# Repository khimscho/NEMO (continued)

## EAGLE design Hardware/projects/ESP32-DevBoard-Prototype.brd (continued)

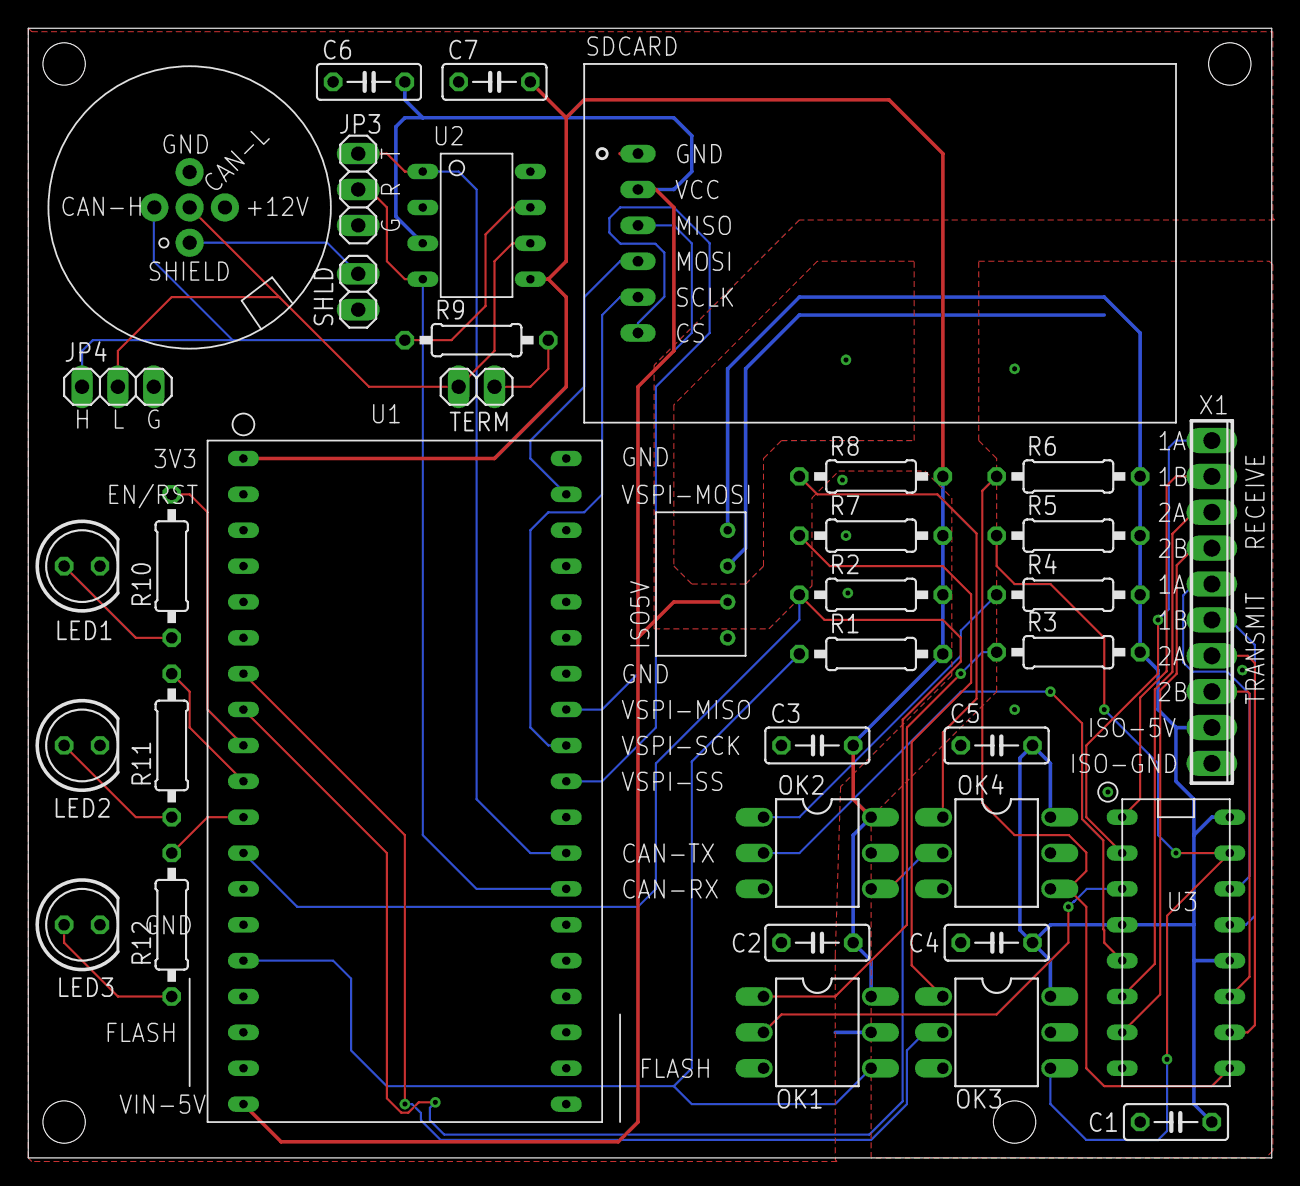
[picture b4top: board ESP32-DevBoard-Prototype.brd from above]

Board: 2 copper layers, 88.1 x 80.0 mm, 37 parts (0 on the bottom side), 41 nets.

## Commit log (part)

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2021-02-16 Fixed bug in StatusLED that was preventing blue channel from working.
2021-02-26 Cleaned up reporting of debugging information (efficiency).
2021-03-05 Added debugging facility for a dummy log manager (i.e., to allow the system to run without SD or eMMC attached).
2021-03-17 Updates to library specifications for devices, and schematic/board to match in order to give better match to actual components; V2.3 of demonstration board.
2021-03-29 Added a metadata packet to the log files that contains logger name and ID.
2021-03-29 Updates to AWS upload functionality.
2021-05-12 Updates to timestamping code to allow for less verbose (or at least controllable verbosity) in output, and to allow for local timestamping of files for testing.
2021-07-04 Updates to design for WIBL, board and schematic, to match new SMPS integration, and other small fixes for layout of power input, and super-capacitor charging circuit.
2021-08-04 Patched around potential divide by zero error in NMEA0183 false-start detection (i.e., auto-inverse).
2021-08-17 Update to configuration to allow for OTA updates to loggers.
2021-08-29 Added configuration parameters and code to allow the baud rate for NMEA0183 to be set (rather than assuming 4800), and to choose whether to boot on BLE or WiFi.
2021-09-04 Added tools to remove duplicate depth records from WIBL files in CSV format, and to plot such files for quite QC.
2021-09-06 Repeat of last commit, this time with actual algorithm.
2021-09-08 Added facility to extract detailed "platform" metadata from the WIBL binary file, and splice into the GeoJSON header before transmission.
2021-09-09 Canonicalised the command language so that all commands with parameters that set state also report the state if the command name alone is given. (Most can also be found by the "configure" command). U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
2021-09-11 Bug fix in NMEA0183 filtering to ensure that no filter IDs mean that everything is accepted (the default case).
2021-09-13 Bug fixes in timestamping code.
2021-11-08 Update to remove binary builds directory from consideration.
2021-11-12 Added counting of motion sensor packets when converting and timestamping, and adjusted filenames created by Qt interface to match logger.
2021-11-15 Added check for data format version when attempting to translate WIBL files during processing (Timestamping.py), and cleaned up error reporting so that exceptions don't cause the code to crash.
2021-11-17 Added limited facility to run known algorithms in AWS processing, based on algorithm packets in the input WIBL file. Initial algorithm is a depth deduplication module. Update to Timestamping.py to su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
2021-11-22 Cleaned up AWS configuration code to use actual JSON capabilities.
2021-12-14 Update to binary file reader script (AWS/Processing/LoggerFile.py) to add support for NMEA0183 packet filter information; updated editing script to allow these to be added post facto.
2021-12-20 Further documentation updates.
2022-02-08 Added check to JSONmetadata constructor to make sure that user input metadata strings (as strings) don't cause problems.
2022-03-08 Stopped tracking local version of extensions for VSCode.
2022-03-13 Added library specific to LSM6DSL used in first run of NEMO-30 loggers.
2022-03-21 Added local scale factors for IMU readings to avoid having to re-compute each time, and set up for actual values in IMU parameter configuration.
2022-04-05 Initial commit of new branch, corrected SDA and SCL crossed connections and rerouted INt1 more appropriately
2022-05-05 Convert from setup.py to pyproject.toml
2022-05-09 Add --version option
2022-05-10 Stub out DataGenerator class
2022-05-11 Implement test for DataGenerator.generate_gga()
2022-05-13 Update test 'test_generate_gga()' to be consistent with later tests; Implement DataGenerator.generate_zda()
2022-05-16 Initial implementation of simulation Engine
2022-05-16 Initial debug of python data simulator
2022-05-18 Update DataGenerator to allow either data or buffer constructor to be used for DataPackets
2022-05-19 Add gitignore; Add test requirements to setup.cfg; Add Jupyter notebook losely documenting local test version of cloud processing script
2022-06-15 Add B12 version 2 and 3 example documents
2022-07-12 Fixed bug (hang-over from a previous version of the API) in timestamp_data.py. This allows the code to work with the current version of AWS/Processing/Timestamping.py.
2022-07-15 Updated ignore file for VSCode
2022-07-27 Add test to cover bug in Attitude packets where little endian flag was not being used for payload packing
2022-07-28 Repurpose simulator_testing.ipynb as local_lambda_testing.ipynb and remove extraneous examples
2022-08-23 Updated test scripts to use new WIBL installed module, rather than calling for sources directly.
2022-11-16 Added instructions on how to add an S3 trigger to AWS Lambdas from the command line.
2022-12-01 Fixed bug in interpolation (all variables have to be returned as NumPy arrays, rather than lists, so they can be sub-set in some algorithms).
2023-01-10 Added scripts to generate a desktop configuration JSON file as required by some of the local implementation of WIBL tools. Updated README to support new additions.
2023-01-28 Updated version information on PCB silk-screen (2.4.0), cleaned up hardware projects directory, renamed main schematic and board to reflect WIBL naming.
2023-02-01 Added copyright statements and file-level comments to REST API prototype.
2023-02-09 Update to documentation for GeoJSON conversion code.
2023-02-21 Added parameter to configure web server interface use.
2023-02-22 Ensured WiFI startup is optional, controlled by the "webserver" command.
2023-02-24 Added "stopped" status to LED specification for hardware, and added call to enable it when in shutdown mode.
2023-02-24 Revised command processor version number to reflect significant changes in commands available.
2023-02-28 Initial addition of a simple webserver interface tool for desktop machines (with GUI).
2023-03-03 Added timeouts to webserver-based GUI to avoid hangs when the logger isn't available, and added GUI to set/reset/load/save algorithm definitions; adjusted firmware handling to facilitate this.
2023-03-05 Added default SSID/password for the WiFi firmware so that on first boot the system needs no configuration to bring up its AP in a default state.
2023-03-06 Update to platform patch code since the UART invert code has been added to the default. The WebServer.cpp code is required to remove a "fix" for Chrome that causes responses to be terminated after th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
2023-03-07 Cosmetic change to syntax list in firmware.
2023-03-09 Make dependency versions consistent across setup.cfg and requirements files
2023-03-10 Update Python data simulator Writer to pass shipname into Metadata constructor
2023-03-21 Bug fix in log conversion C++ (update to v 1.3 serialisation version, adds IMU version information), DCDB upload, and name/uniqueid clarification in Python file parser.
2023-04-08 Added check for NMEA0183 sentences being valid (i.e., have a checksum, and match it) prior to them being written to file.
2023-04-21 Add documentation to README for procwibl command; Add script to perform integration testing using wibl command line tool
2023-05-03 Initial debugging of ECS creation script
2023-06-29 Add proper script entry point to make running in a debugger easier
2023-06-30 Added WebServer.h to platform patches so that it matches the WebServer.cpp; it appears that the signature of _streamFileCore() changed recently, and causes problems with compilation.
2023-07-14 Updates to formatting of firmware internal website, and added prototype design for status, metadata management, algorithm requests.
2023-07-15 Updates to JavaScript functionality for logger firmware internal website.
2023-08-02 Add PowerShell script to convert YDVR files to WIBL format using compiled version of WIBL LogConvert
2023-08-22 logconvert: added ability to incorporate metadata into the converted WIBL file on creation (rather than having to use wibl editwibl later).
2023-09-05 dcdb_upload: Fix broken handling of local notifier configuration
2023-09-07 datasim: add ability to randomly generate duplicate data; algorithms: Add unit test for deduplication algorithm
2023-09-13 wibl-python: algorithms: Refactor algorithm discovery from timestamping code to fileloader to allow algorithms to be applied to on-load phase; move algorithm code into wibl.core to avoid circular imp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
2023-09-15 Merged in feature-aws-updates (pull request #13)
    Feature aws updates
    * wibl-python: cloud: Update lambdas to non-deprecated Python 3.11, also update to ARM64
    * wibl-python: Update to csbschema version 1.1.1
    Approved-by: Brian Calder
2023-10-11 wibl-python: scripts: Add example script to batch convert YDVR data to WIBL using logconvert
2023-11-13 wibl-python: fix broken relative imports
2023-11-20 LogConvert: Add Docker configuration for building against AWS Linux lambda environment
2023-11-28 wibl-python: Add DCDB submission data management script; Re-work outline documentation of data management scripts
2023-11-28 (Firmware) Rationalised includes for JS in website to minimise size after inlining for implementation.
2023-11-30 wibl-python: data preview: more experiments with PyGMT and Cartopy
2023-12-01 (Firmware): Functionality for an upload handshake token to be stored in logger, and facilities to set it in website and DesktopUI. Update to website and DesktopUI for firmware version display. Update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
2023-12-03 (Firmware): Update to syntax list for "token" command; made /heartbeat API endpoint generate results of a '"status" command, rather than just a serial number.
2023-12-05 wibl-python: data preview: initial GMT Docker config
2023-12-06 wibl-python: data preview: GMT zsh script: add title
2023-12-06 wibl-python: simulator: Update starting longitude of simulator to be over water instead of land
2023-12-11 wibl-python: data preview: start cleaning up Python version of plotting shell script
2023-12-12 (Firmware): Updated release notes for 1.5.0
2023-12-12 wibl-python: data preview: filter soundings greater than reasonable values; plot soundings with a color map; add colorbar for soundings; make map bounding box scaling automatic
2023-12-13 wibl-python: data preview: Merge GeoJSON files before rasterizing
2023-12-15 wibl-python: data preview: library implementation of map_soundings and test
2023-12-18 wibl-python: data preview: start Dockerfile for visualization lambda
2023-12-21 wibl-python: Continue refactor of commands into wibl.command sub-module
2023-12-23 (Firmware): Bug-fixes to make sure that parameter files and NVM files exist before we attempt to open (by creating an empty file). Added debug configuration to allow the exception decoder to be used 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
2024-01-03 wibl-python: data preview: Script downloading of GEBCO data to EFS volume
2024-01-04 wibl-python: data preview: Add amazon-efs-utils to lambda Dockerfile to allow mounting of EFS volumes
2024-01-05 (Firmware): updated copyright statements on all files and utilities.
2024-01-05 wibl-python: make gdal_rasterize be quiet
2024-01-10 wibl-python: Update dependency specifications to specify compatible releases, especially in advance of NumPy 2.0, which has lots of small breaking changes due to API clean-up
2024-01-10 wibl-python: Fix requests dependency to be compatible with Python 3.12
2024-01-18 (Firmware): bug-fixes and corrections for TLS and BasicAuth on auto-upload service.
2024-01-19 wibl-python: data preview: Remove debug line from lambda configuration script
2024-01-29 Small modification to match variant setup on reference machine.
2024-02-09 datamgmt: Dockerfile: parameterize wibl repo commit; Begin adding container usage instructures
2024-02-09 datamgmt: Move README.md and BUILDING.md files to containers directory
